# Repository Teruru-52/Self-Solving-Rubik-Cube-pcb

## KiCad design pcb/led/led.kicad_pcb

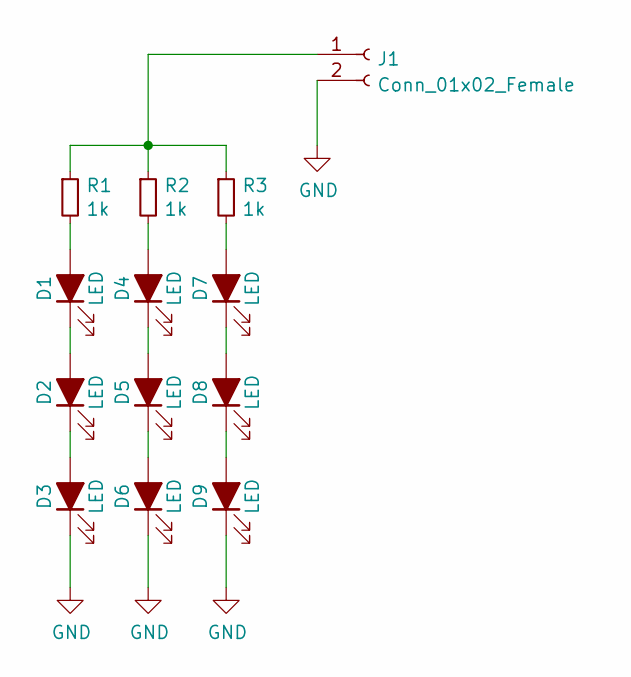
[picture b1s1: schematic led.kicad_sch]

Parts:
D1, D2, D3, D4, D5, D6, D7, D8, D9: LED; OSW5DLS1C1A
J1: Conn_01x02_Female; PinSocket_1x02_P2.54mm_Vertical
R1, R2, R3: 1k; R_0805_2012Metric_Pad1.20x1.40mm_HandSolder

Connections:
GND: D3.1 (K), D6.1 (K), D9.1 (K), J1.2
unnamed: D1.1 (K), D2.2 (A)
unnamed: D1.2 (A), R1.2
unnamed: D2.1 (K), D3.2 (A)
unnamed: D4.1 (K), D5.2 (A)
unnamed: D4.2 (A), R2.2
unnamed: D5.1 (K), D6.2 (A)
unnamed: D7.1 (K), D8.2 (A)
unnamed: D7.2 (A), R3.2
unnamed: D8.1 (K), D9.2 (A)
unnamed: J1.1, R1.1, R2.1, R3.1

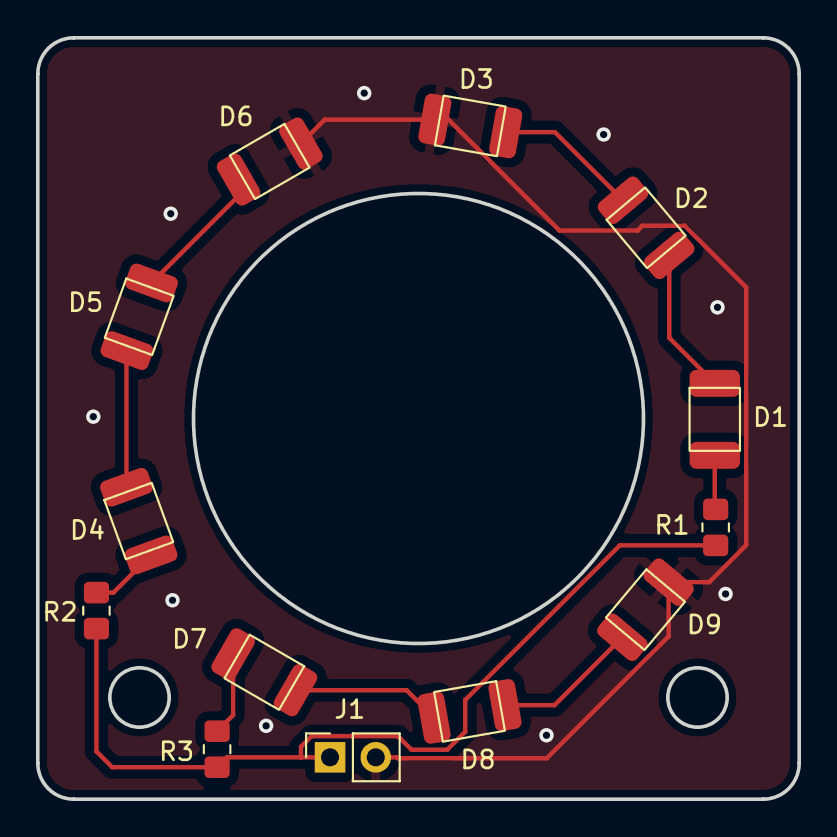
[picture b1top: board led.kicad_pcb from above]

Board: 2 copper layers, 42.3 x 42.3 mm, 13 parts (0 on the bottom side), 11 nets.

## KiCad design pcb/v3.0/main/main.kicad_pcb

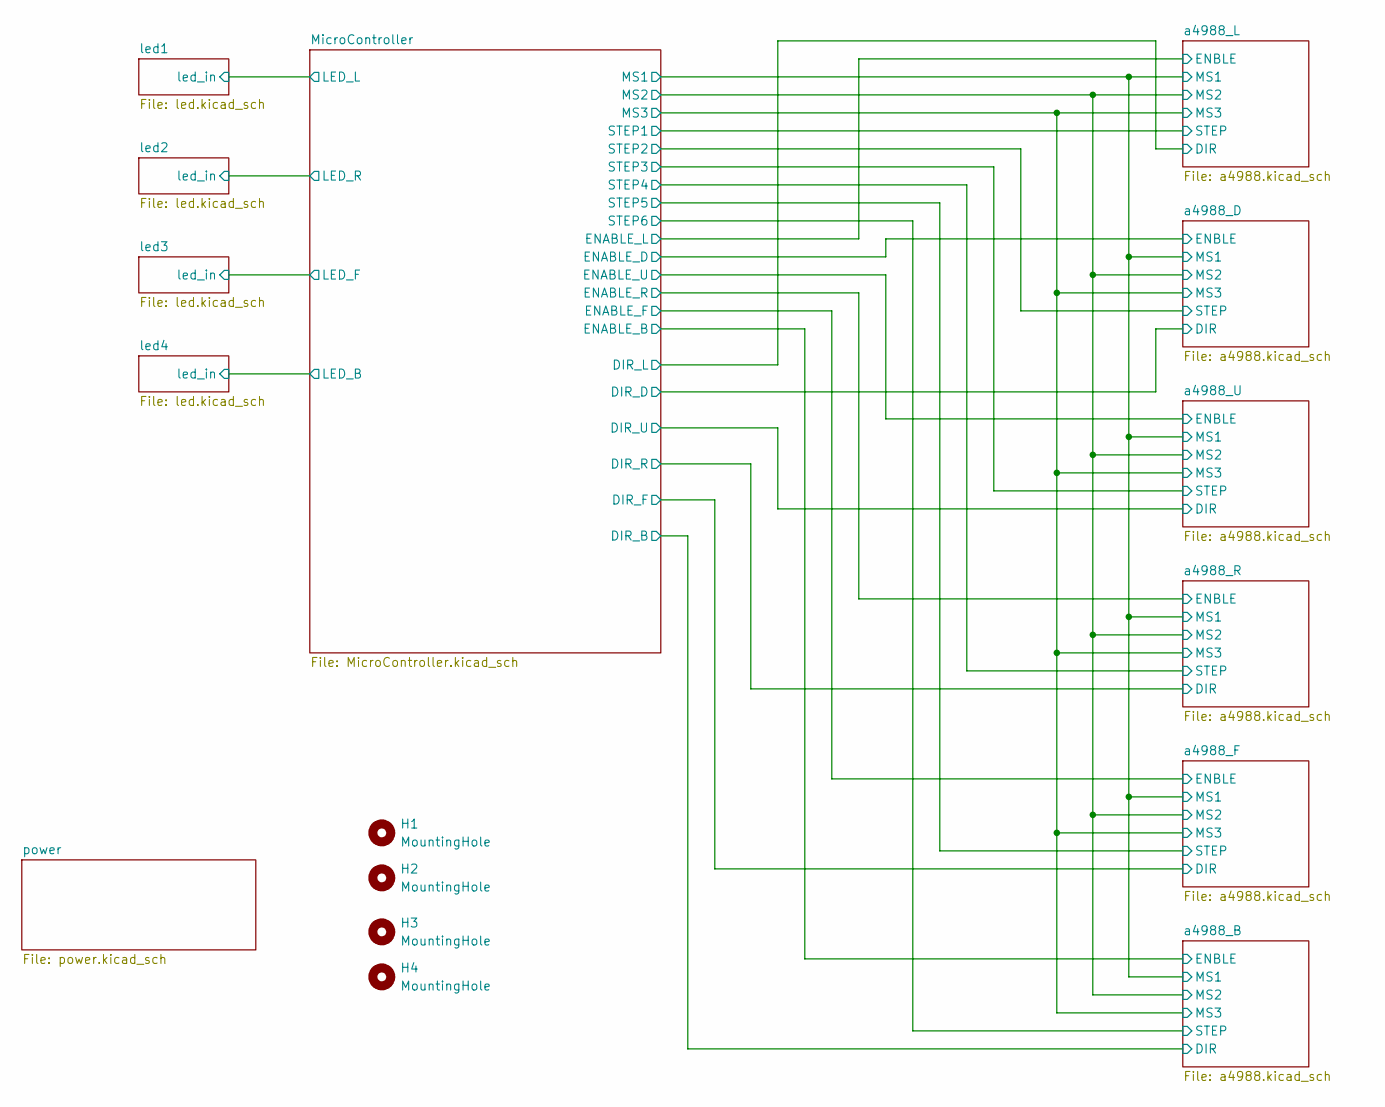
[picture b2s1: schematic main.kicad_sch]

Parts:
H1, H2, H3, H4: MountingHole; MountingHole_3.2mm_M3

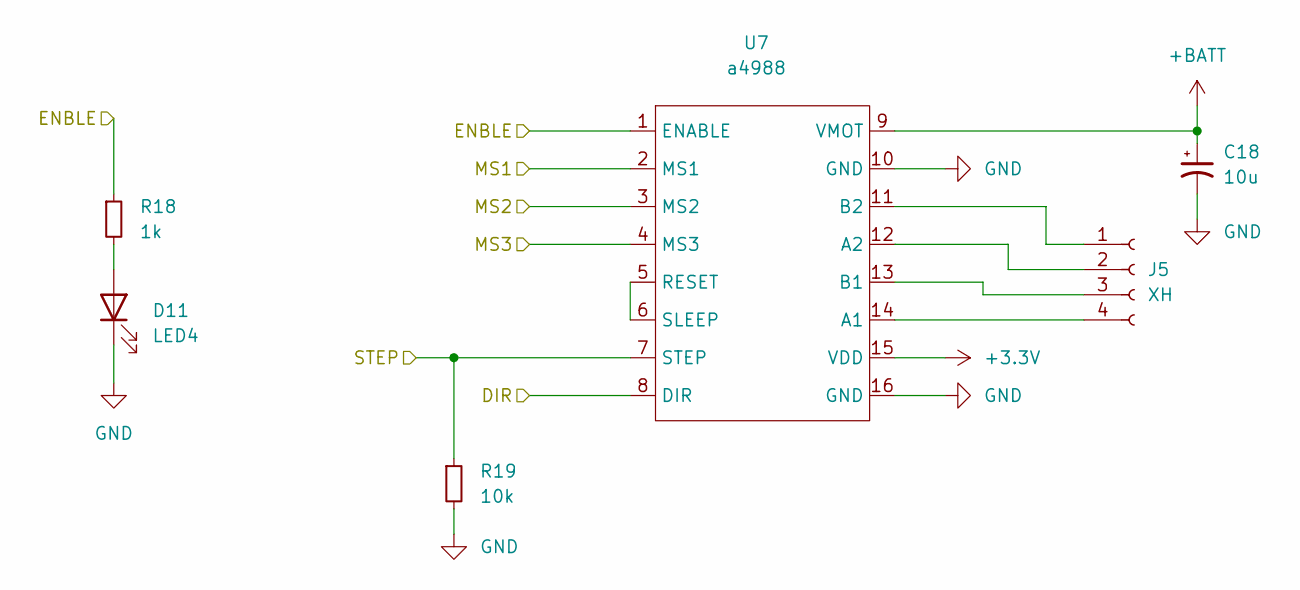
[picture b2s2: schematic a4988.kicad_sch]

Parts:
C18: 10u; CP_Radial_D5.0mm_P2.50mm
D11: LED4; LED_0603_1608Metric
J5: XH; JST_XH_B4B-XH-A_1x04_P2.50mm_Vertical
R18: 1k; R_0603_1608Metric_Pad0.98x0.95mm_HandSolder
R19: 10k; R_0603_1608Metric
U7: a4988

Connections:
+3.3V: U7.15 (VDD); also elsewhere on the board
+BATT: C18.1, U7.9 (VMOT); also elsewhere on the board
/MicroController/DIR_U: U7.8 (DIR); also elsewhere on the board
/MicroController/ENABLE_U: R18.1, U7.1 (ENABLE); also elsewhere on the board
/MicroController/MS1: U7.2 (MS1); also elsewhere on the board
/MicroController/MS2: U7.3 (MS2); also elsewhere on the board
/MicroController/MS3: U7.4 (MS3); also elsewhere on the board
/MicroController/STEP1: R19.1, U7.7 (STEP); also elsewhere on the board
GND: C18.2, D11.1 (K), R19.2, U7.10 (GND), U7.16 (GND); also elsewhere on the board
unnamed: D11.2 (A), R18.2
unnamed: J5.1, U7.11 (B2)
unnamed: J5.2, U7.12 (A2)
unnamed: J5.3, U7.13 (B1)
unnamed: J5.4, U7.14 (A1)
unnamed: U7.5 (RESET), U7.6 (SLEEP)

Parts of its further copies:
C17, C19, C20, C21, C22: 10u; CP_Radial_D5.0mm_P2.50mm
D10, D12, D13, D14, D15: LED4; LED_0603_1608Metric
J4, J6, J7, J8, J11: XH; JST_XH_B4B-XH-A_1x04_P2.50mm_Vertical
R16, R20, R22, R24, R30: 1k; R_0603_1608Metric_Pad0.98x0.95mm_HandSolder
R17, R21, R23, R25, R31: 10k; R_0603_1608Metric
U6, U8, U9, U10, U11: a4988

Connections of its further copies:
+3.3V: U6.15 (VDD), U8.15 (VDD), U9.15 (VDD), U10.15 (VDD), U11.15 (VDD); also elsewhere on the board
+BATT: C17.1, C19.1, C20.1, C21.1, C22.1, U6.9 (VMOT), U8.9 (VMOT), U9.9 (VMOT), U10.9 (VMOT), U11.9 (VMOT); also elsewhere on the board
/MicroController/DIR_B: U10.8 (DIR); also elsewhere on the board
/MicroController/DIR_D: U6.8 (DIR); also elsewhere on the board
/MicroController/DIR_F: U9.8 (DIR); also elsewhere on the board
/MicroController/DIR_L: U8.8 (DIR); also elsewhere on the board
/MicroController/DIR_R: U11.8 (DIR); also elsewhere on the board
/MicroController/ENABLE_B: R24.1, U10.1 (ENABLE); also elsewhere on the board
/MicroController/ENABLE_D: R16.1, U6.1 (ENABLE); also elsewhere on the board
/MicroController/ENABLE_F: R22.1, U9.1 (ENABLE); also elsewhere on the board
/MicroController/ENABLE_L: R20.1, U8.1 (ENABLE); also elsewhere on the board
/MicroController/ENABLE_R: R30.1, U11.1 (ENABLE); also elsewhere on the board
/MicroController/MS1: U6.2 (MS1), U8.2 (MS1), U9.2 (MS1), U10.2 (MS1), U11.2 (MS1); also elsewhere on the board
/MicroController/MS2: U6.3 (MS2), U8.3 (MS2), U9.3 (MS2), U10.3 (MS2), U11.3 (MS2); also elsewhere on the board
/MicroController/MS3: U6.4 (MS3), U8.4 (MS3), U9.4 (MS3), U10.4 (MS3), U11.4 (MS3); also elsewhere on the board
/MicroController/STEP1: R17.1, R21.1, R23.1, R25.1, R31.1, U6.7 (STEP), U8.7 (STEP), U9.7 (STEP), U10.7 (STEP), U11.7 (STEP); also elsewhere on the board
GND: C17.2, C19.2, C20.2, C21.2, C22.2, D10.1 (K), D12.1 (K), D13.1 (K), D14.1 (K), D15.1 (K), R17.2, R21.2, R23.2, R25.2, R31.2, U6.10 (GND), U6.16 (GND), U8.10 (GND), U8.16 (GND), U9.10 (GND), U9.16 (GND), U10.10 (GND), U10.16 (GND), U11.10 (GND), U11.16 (GND); also elsewhere on the board
unnamed: D10.2 (A), R16.2
unnamed: D12.2 (A), R20.2
unnamed: D13.2 (A), R22.2
unnamed: D14.2 (A), R24.2
unnamed: D15.2 (A), R30.2
unnamed: J4.1, U6.11 (B2)
unnamed: J4.2, U6.12 (A2)
unnamed: J4.3, U6.13 (B1)
unnamed: J4.4, U6.14 (A1)
unnamed: J6.1, U8.11 (B2)
unnamed: J6.2, U8.12 (A2)
unnamed: J6.3, U8.13 (B1)
unnamed: J6.4, U8.14 (A1)
unnamed: J7.1, U9.11 (B2)
unnamed: J7.2, U9.12 (A2)
unnamed: J7.3, U9.13 (B1)
unnamed: J7.4, U9.14 (A1)
unnamed: J8.1, U10.11 (B2)
unnamed: J8.2, U10.12 (A2)
unnamed: J8.3, U10.13 (B1)
unnamed: J8.4, U10.14 (A1)
unnamed: J11.1, U11.11 (B2)
unnamed: J11.2, U11.12 (A2)
unnamed: J11.3, U11.13 (B1)
unnamed: J11.4, U11.14 (A1)
unnamed: U6.5 (RESET), U6.6 (SLEEP)
unnamed: U8.5 (RESET), U8.6 (SLEEP)
unnamed: U9.5 (RESET), U9.6 (SLEEP)
unnamed: U10.5 (RESET), U10.6 (SLEEP)
unnamed: U11.5 (RESET), U11.6 (SLEEP)

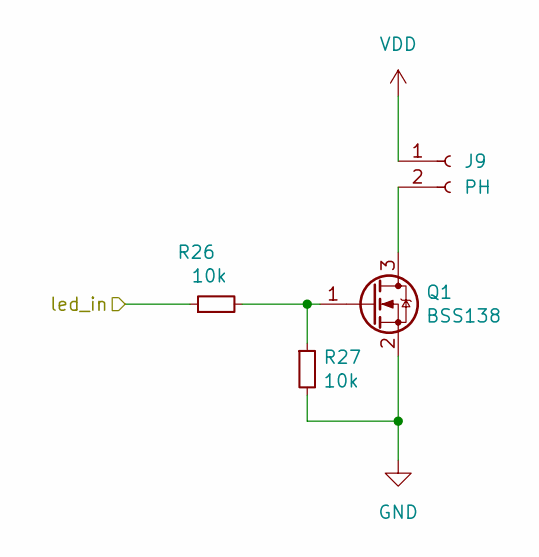
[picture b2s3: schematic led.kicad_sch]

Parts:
J9: PH; JST_PH_S2B-PH-K_1x02_P2.00mm_Horizontal
Q1: BSS138; SOT-23
R26, R27: 10k; R_0603_1608Metric_Pad0.98x0.95mm_HandSolder

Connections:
/MicroController/LED_R: R26.1; also elsewhere on the board
GND: Q1.2 (S), R27.2; also elsewhere on the board
unnamed: J9.2, Q1.3 (D)
unnamed: Q1.1 (G), R26.2, R27.1
VDD: J9.1; also elsewhere on the board

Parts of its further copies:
J10, J12, J13: PH; JST_PH_S2B-PH-K_1x02_P2.00mm_Horizontal
Q2, Q3, Q4: BSS138; SOT-23
R28, R29, R32, R33, R34, R35: 10k; R_0603_1608Metric_Pad0.98x0.95mm_HandSolder

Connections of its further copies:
/MicroController/LED_B: R34.1; also elsewhere on the board
/MicroController/LED_F: R32.1; also elsewhere on the board
/MicroController/LED_L: R28.1; also elsewhere on the board
GND: Q2.2 (S), Q3.2 (S), Q4.2 (S), R29.2, R33.2, R35.2; also elsewhere on the board
unnamed: J10.2, Q2.3 (D)
unnamed: J12.2, Q3.3 (D)
unnamed: J13.2, Q4.3 (D)
unnamed: Q2.1 (G), R28.2, R29.1
unnamed: Q3.1 (G), R32.2, R33.1
unnamed: Q4.1 (G), R34.2, R35.1
VDD: J10.1, J12.1, J13.1; also elsewhere on the board

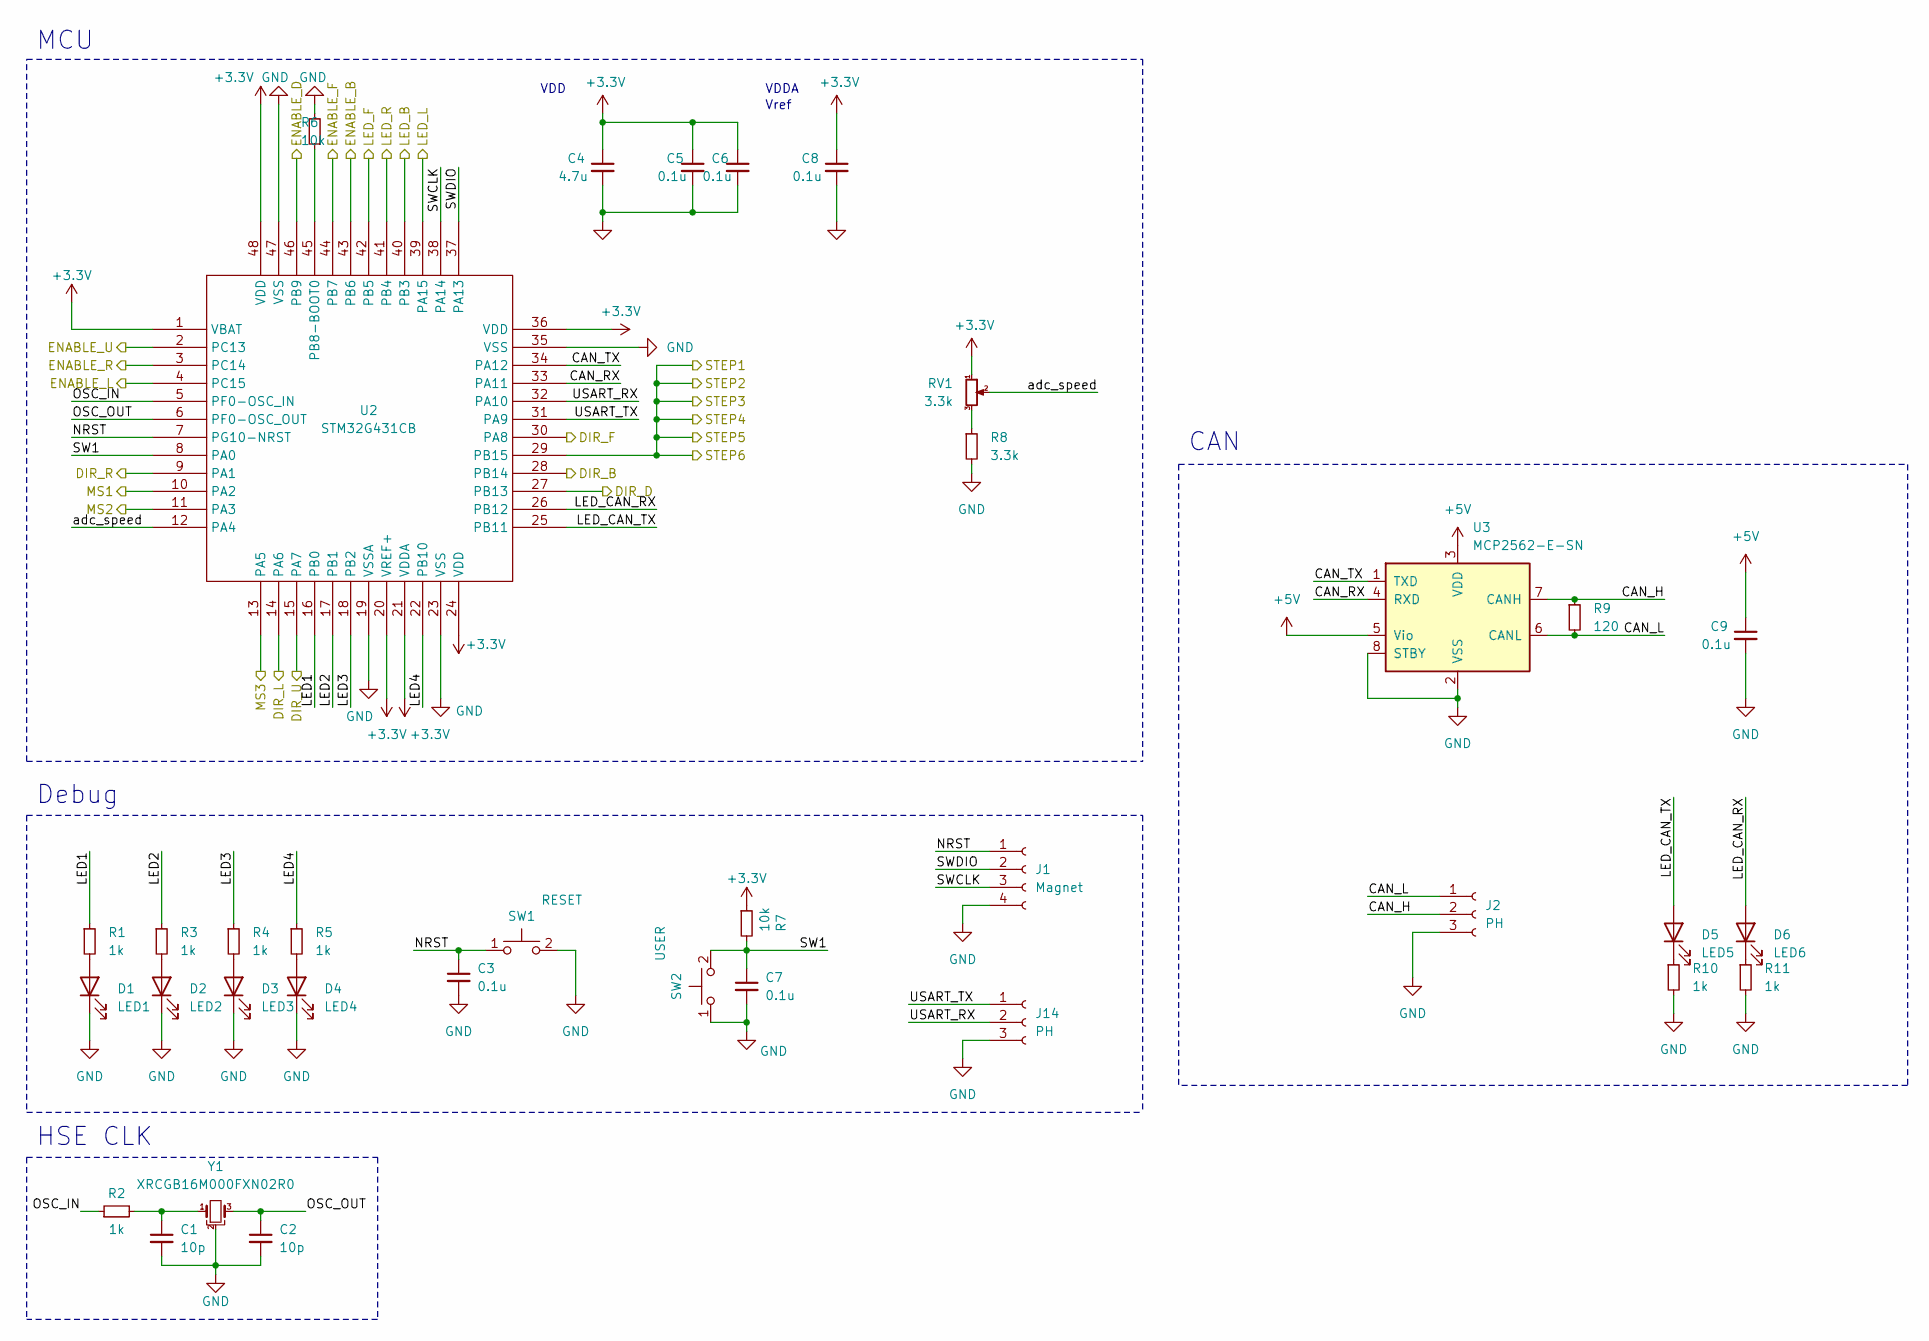
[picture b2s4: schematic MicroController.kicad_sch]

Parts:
C1, C2: 10p; C_0402_1005Metric_Pad0.74x0.62mm_HandSolder
C3, C7: 0.1u; C_0603_1608Metric_Pad1.08x0.95mm_HandSolder
C4: 4.7u; C_0603_1608Metric
C5, C6, C8, C9: 0.1u; C_0603_1608Metric
D1: LED1; LED_0603_1608Metric
D2: LED2; LED_0603_1608Metric
D3: LED3; LED_0603_1608Metric
D4: LED4; LED_0603_1608Metric
D5: LED5; LED_0603_1608Metric
D6: LED6; LED_0603_1608Metric
J1: Magnet; PinSocket_1x04_P2.54mm_Vertical
J2, J14: PH; JST_PH_S3B-PH-K_1x03_P2.00mm_Horizontal
R1, R3, R4, R5, R10, R11: 1k; R_0603_1608Metric_Pad0.98x0.95mm_HandSolder
R2: 1k; R_0402_1005Metric_Pad0.72x0.64mm_HandSolder
R6, R7: 10k; R_0603_1608Metric_Pad0.98x0.95mm_HandSolder
R8: 3.3k; R_0603_1608Metric_Pad0.98x0.95mm_HandSolder
R9: 120; R_0603_1608Metric_Pad0.98x0.95mm_HandSolder
RV1: 3.3k; Potentiometer_Vishay_T73YP_Vertical
SW1: RESET; TVAF06-A020B-R
SW2: USER; TVAF06-A020B-R
U2: STM32G431CB; LQFP-48_7x7mm_P0.5mm
U3: MCP2562-E-SN; SOIC-8_3.9x4.9mm_P1.27mm
Y1: XRCGB16M000FXN02R0; XRCGB

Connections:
+3.3V: C4.1, C5.1, C6.1, C8.1, R7.1, RV1.1, U2.1 (VBAT), U2.20 (VREF+), U2.21 (VDDA), U2.24 (VDD), U2.36 (VDD), U2.48 (VDD); also elsewhere on the board
+5V: C9.1, U3.3 (VDD), U3.5 (Vio); also elsewhere on the board
/MicroController/CAN_H: J2.2, R9.1, U3.7 (CANH)
/MicroController/CAN_L: J2.1, R9.2, U3.6 (CANL)
/MicroController/CAN_RX: U2.33 (PA11), U3.4 (RXD)
/MicroController/CAN_TX: U2.34 (PA12), U3.1 (TXD)
/MicroController/DIR_B: U2.28 (PB14); also elsewhere on the board
/MicroController/DIR_D: U2.27 (PB13); also elsewhere on the board
/MicroController/DIR_F: U2.30 (PA8); also elsewhere on the board
/MicroController/DIR_L: U2.14 (PA6); also elsewhere on the board
/MicroController/DIR_R: U2.9 (PA1); also elsewhere on the board
/MicroController/DIR_U: U2.15 (PA7); also elsewhere on the board
/MicroController/ENABLE_B: U2.43 (PB6); also elsewhere on the board
/MicroController/ENABLE_D: U2.46 (PB9); also elsewhere on the board
/MicroController/ENABLE_F: U2.44 (PB7); also elsewhere on the board
/MicroController/ENABLE_L: U2.4 (PC15); also elsewhere on the board
/MicroController/ENABLE_R: U2.3 (PC14); also elsewhere on the board
/MicroController/ENABLE_U: U2.2 (PC13); also elsewhere on the board
/MicroController/LED1: R1.1, U2.16 (PB0)
/MicroController/LED2: R3.1, U2.17 (PB1)
/MicroController/LED3: R4.1, U2.18 (PB2)
/MicroController/LED4: R5.1, U2.22 (PB10)
/MicroController/LED_B: U2.40 (PB3); also elsewhere on the board
/MicroController/LED_CAN_RX: D6.2 (A), U2.26 (PB12)
/MicroController/LED_CAN_TX: D5.2 (A), U2.25 (PB11)
/MicroController/LED_F: U2.42 (PB5); also elsewhere on the board
/MicroController/LED_L: U2.39 (PA15); also elsewhere on the board
/MicroController/LED_R: U2.41 (PB4); also elsewhere on the board
/MicroController/MS1: U2.10 (PA2); also elsewhere on the board
/MicroController/MS2: U2.11 (PA3); also elsewhere on the board
/MicroController/MS3: U2.13 (PA5); also elsewhere on the board
/MicroController/NRST: C3.1, J1.1, SW1.1, U2.7 (PG10-NRST)
/MicroController/OSC_IN: R2.1, U2.5 (PF0-OSC_IN)
/MicroController/OSC_OUT: C2.1, U2.6 (PF0-OSC_OUT), Y1.3
/MicroController/STEP1: U2.29 (PB15); also elsewhere on the board
/MicroController/SW1: C7.1, R7.2, SW2.2, U2.8 (PA0)
/MicroController/SWCLK: J1.3, U2.38 (PA14)
/MicroController/SWDIO: J1.2, U2.37 (PA13)
/MicroController/USART_RX: J14.2, U2.32 (PA10)
/MicroController/USART_TX: J14.1, U2.31 (PA9)
/MicroController/adc_speed: RV1.2, U2.12 (PA4)
GND: C1.2, C2.2, C3.2, C4.2, C5.2, C6.2, C7.2, C8.2, C9.2, D1.1 (K), D2.1 (K), D3.1 (K), D4.1 (K), J1.4, J2.3, J14.3, R6.2, R8.2, R10.2, R11.2, SW1.2, SW2.1, U2.19 (VSSA), U2.23 (VSS), U2.35 (VSS), U2.47 (VSS), U3.2 (VSS), U3.8 (STBY), Y1.2; also elsewhere on the board
unnamed: C1.1, R2.2, Y1.1
unnamed: D1.2 (A), R1.2
unnamed: D2.2 (A), R3.2
unnamed: D3.2 (A), R4.2
unnamed: D4.2 (A), R5.2
unnamed: D5.1 (K), R10.1
unnamed: D6.1 (K), R11.1
unnamed: R8.1, RV1.3
unnamed: R6.1, U2.45 (PB8-BOOT0)

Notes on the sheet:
Vref
VDD
MCU
CAN
VDDA
Debug
HSE CLK

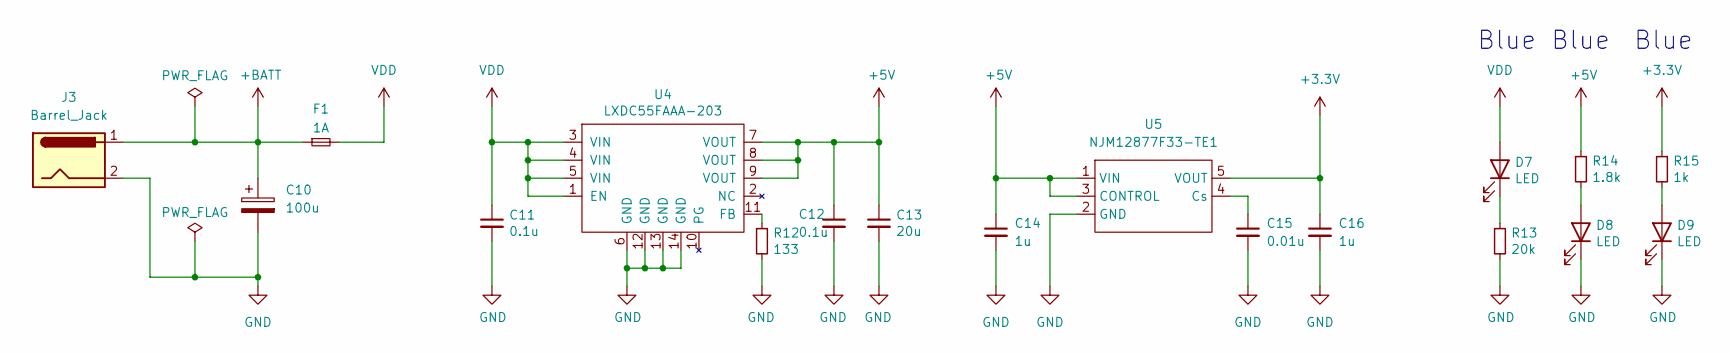
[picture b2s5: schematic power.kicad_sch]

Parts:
C10: 100u; CP_Radial_D10.0mm_P5.00mm
C11, C12: 0.1u; C_0603_1608Metric_Pad1.08x0.95mm_HandSolder
C13: 20u; C_0603_1608Metric_Pad1.08x0.95mm_HandSolder
C14, C16: 1u; C_0603_1608Metric_Pad1.08x0.95mm_HandSolder
C15: 0.01u; C_0603_1608Metric_Pad1.08x0.95mm_HandSolder
D7, D8, D9: LED; LED_0603_1608Metric
F1: 1A; Fuse_1206_3216Metric
J3: Barrel_Jack; BarrelJack_Horizontal
R12: 133; R_1206_3216Metric_Pad1.30x1.75mm_HandSolder
R13: 20k; R_0603_1608Metric_Pad0.98x0.95mm_HandSolder
R14: 1.8k; R_0603_1608Metric_Pad0.98x0.95mm_HandSolder
R15: 1k; R_0603_1608Metric_Pad0.98x0.95mm_HandSolder
U4: LXDC55FAAA-203; LXDC55FAAA203
U5: NJM12877F33-TE1; SOT-23-5_HandSoldering

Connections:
+3.3V: C16.1, R15.1, U5.5 (VOUT); also elsewhere on the board
+5V: C12.1, C13.1, C14.1, R14.1, U4.7 (VOUT), U4.8 (VOUT), U4.9 (VOUT), U5.1 (VIN), U5.3 (CONTROL); also elsewhere on the board
+BATT: C10.1, F1.1, J3.1; also elsewhere on the board
GND: C10.2, C11.2, C12.2, C13.2, C14.2, C15.2, C16.2, D8.1 (K), D9.1 (K), J3.2, R12.2, R13.2, U4.6 (GND), U4.12 (GND), U4.13 (GND), U4.14 (GND), U5.2 (GND); also elsewhere on the board
unnamed: D7.1 (K), R13.1
unnamed: D8.2 (A), R14.2
unnamed: D9.2 (A), R15.2
unnamed: R12.1, U4.11 (FB)
unnamed: C15.1, U5.4 (Cs)
VDD: C11.1, D7.2 (A), F1.2, U4.1 (EN), U4.3 (VIN), U4.4 (VIN), U4.5 (VIN); also elsewhere on the board

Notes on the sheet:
Blue

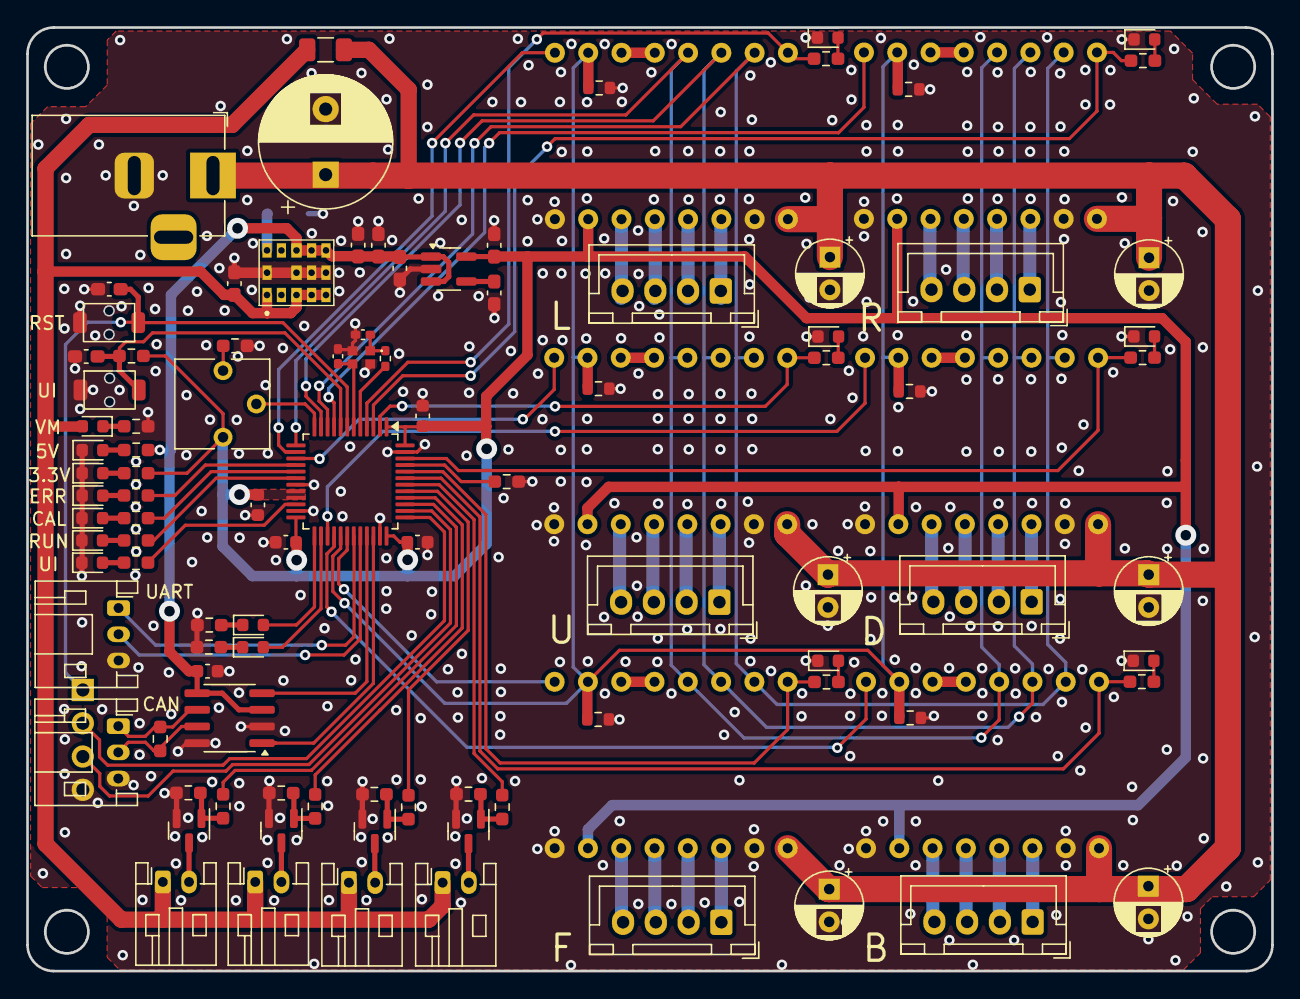
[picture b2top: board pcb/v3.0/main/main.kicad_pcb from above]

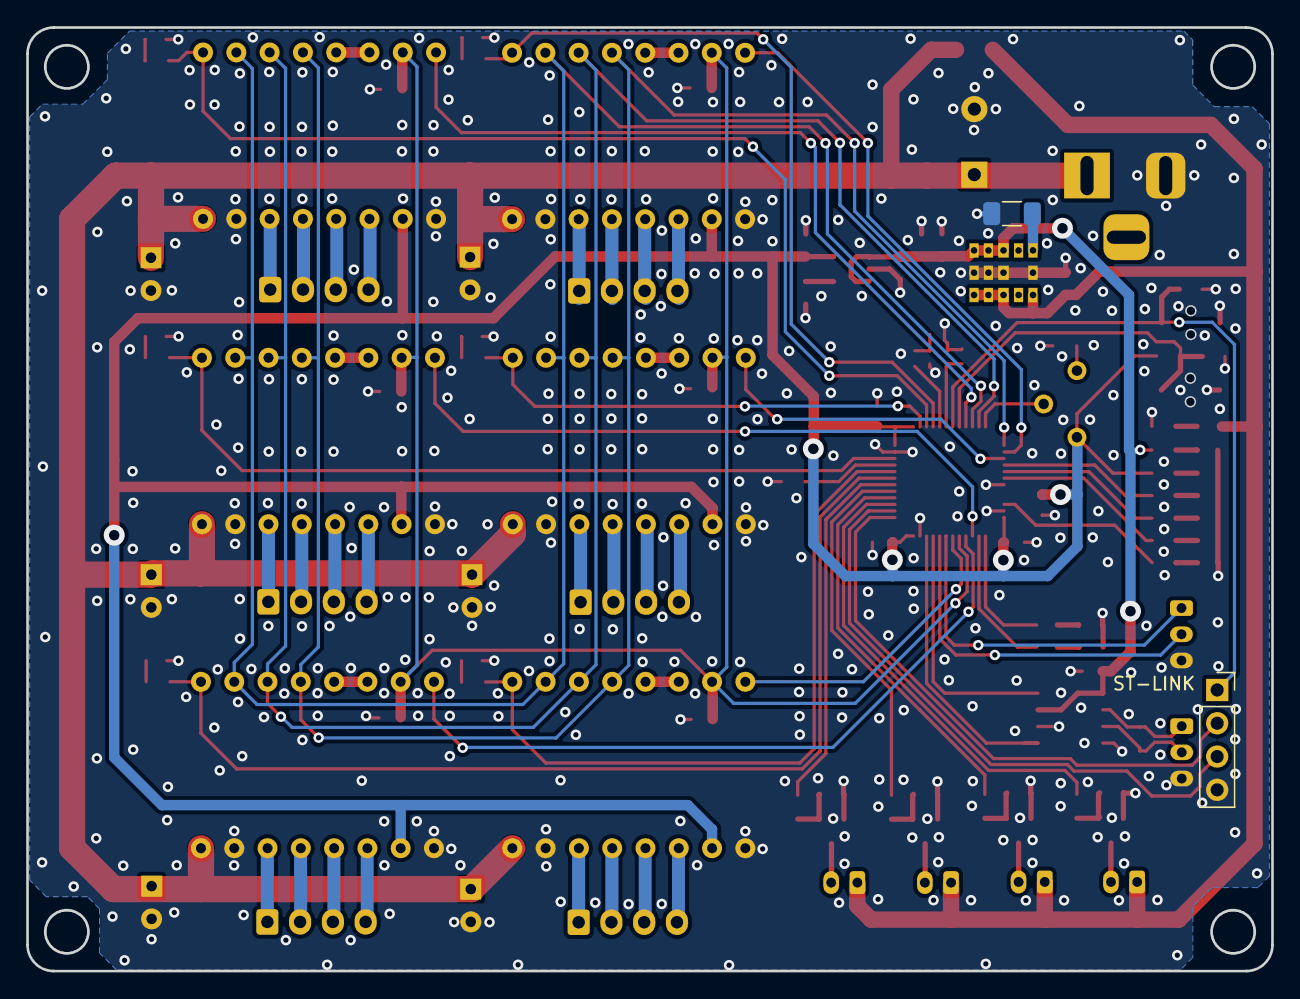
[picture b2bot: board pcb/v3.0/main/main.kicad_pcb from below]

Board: 2 copper layers, 95.0 x 72.0 mm, 109 parts (2 on the bottom side), 102 nets.

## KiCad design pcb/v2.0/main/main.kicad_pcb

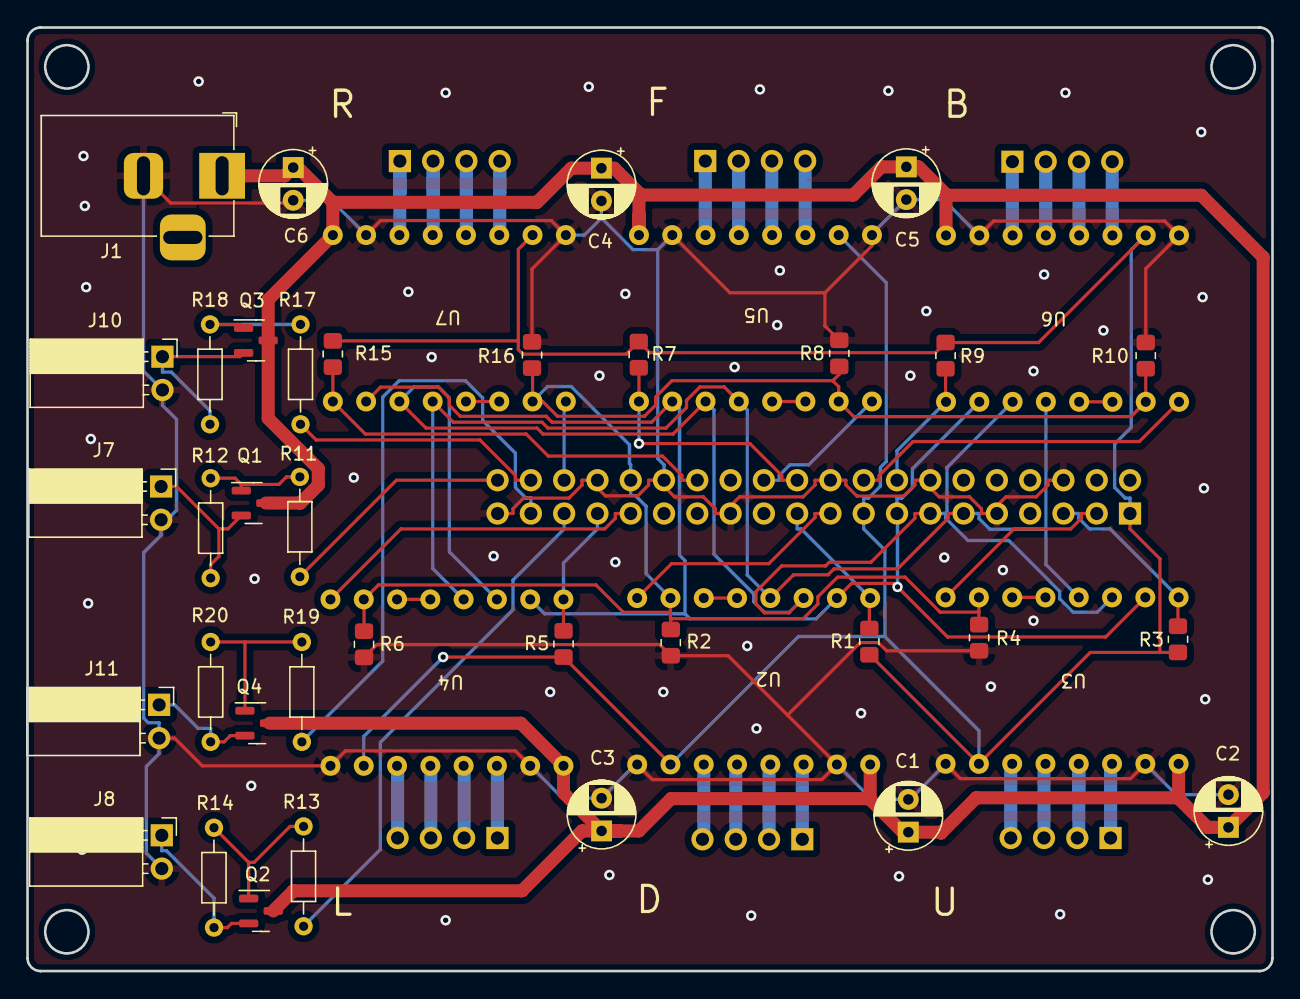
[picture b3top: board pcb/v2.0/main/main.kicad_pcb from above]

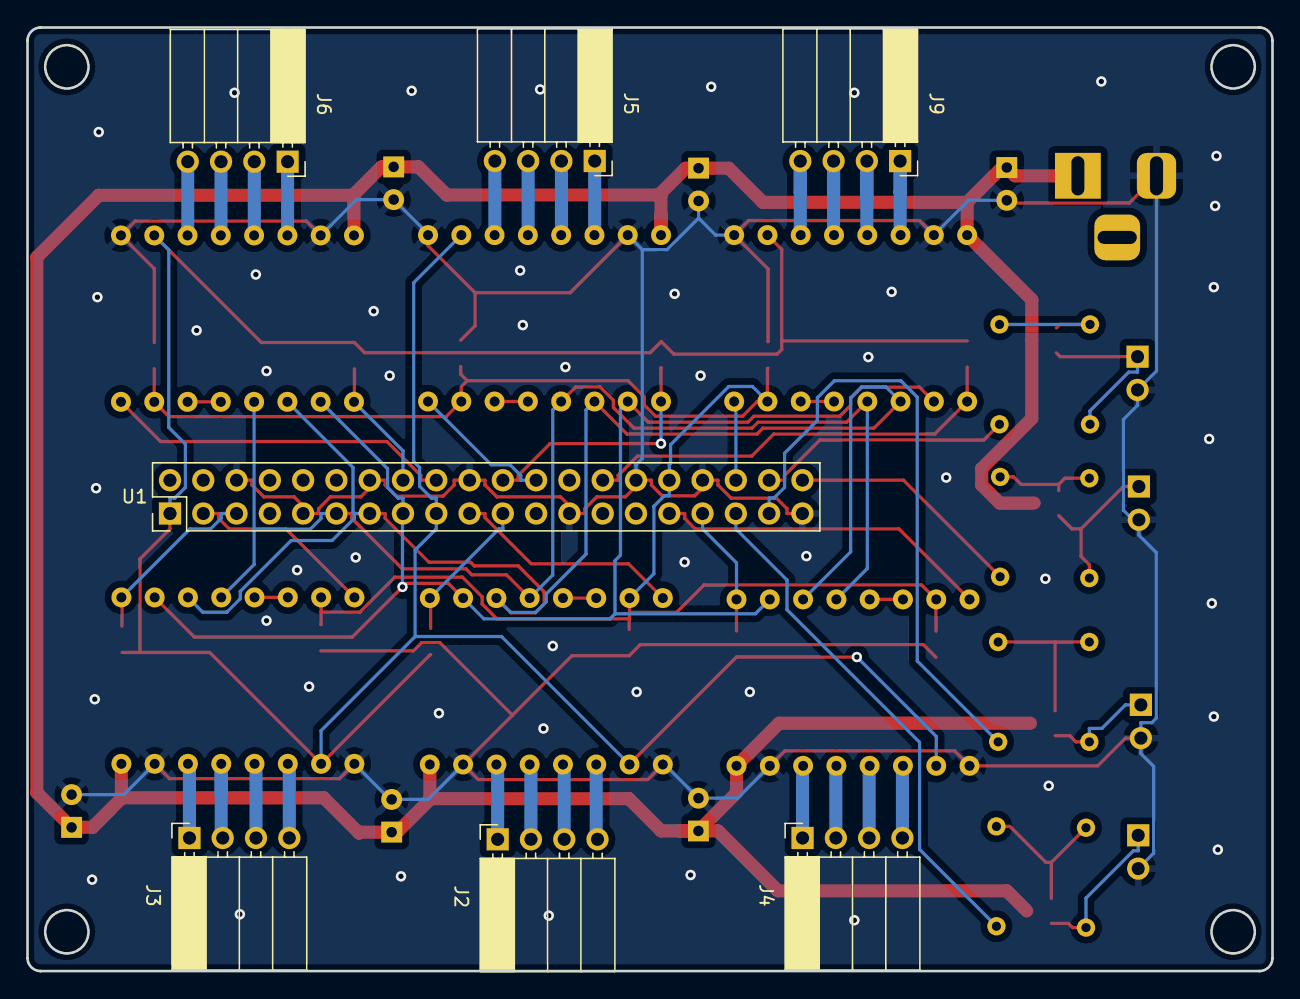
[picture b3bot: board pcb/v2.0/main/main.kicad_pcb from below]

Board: 2 copper layers, 95.0 x 72.0 mm, 48 parts (7 on the bottom side), 61 nets.

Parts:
C1, C2, C3, C4, C5, C6: 10u; CP_Radial_D5.0mm_P2.50mm
J1: Barrel_Jack; BarrelJack_Horizontal
J2, J3, J4, J5, J6, J9: Conn_01x04_Female; PinSocket_1x04_P2.54mm_Horizontal
J7, J8, J10, J11: Conn_01x02_Female; PinSocket_1x02_P2.54mm_Horizontal
Q1, Q2, Q3, Q4: BSS138; SOT-23
R1, R2, R3, R4, R5, R6, R7, R8, R9, R10, R15, R16: 10k; R_0805_2012Metric_Pad1.20x1.40mm_HandSolder
R11, R12, R13, R14, R17, R18, R19, R20: 10k; R_Axial_DIN0204_L3.6mm_D1.6mm_P7.62mm_Horizontal
U1: RaspberryPi4; PinHeader_2x20_P2.54mm_Vertical
U2, U3, U4, U5, U6, U7: a4988

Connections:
+3.3V: R1.1, R3.1, R5.1, R7.1, R9.1, R15.1, U1.1 (3V3), U1.17 (3V3), U2.15 (VDD), U3.15 (VDD), U4.15 (VDD), U5.15 (VDD), U6.15 (VDD), U7.15 (VDD)
+BATT: C1.1, C2.1, C3.1, C4.1, C5.1, C6.1, J1.1, Q1.3 (D), Q2.3 (D), Q3.3 (D), Q4.3 (D), U2.9 (VMOT), U3.9 (VMOT), U4.9 (VMOT), U5.9 (VMOT), U6.9 (VMOT), U7.9 (VMOT)
/MicroController/DIR_B: U1.18 (GPIO24), U6.8 (DIR)
/MicroController/DIR_D: U1.19 (GPIO10/MOSI), U2.8 (DIR)
/MicroController/DIR_F: U1.24 (GPIO8/CE0), U5.8 (DIR)
/MicroController/DIR_L: U1.31 (GPIO6), U4.8 (DIR)
/MicroController/DIR_R: U1.36 (GPIO16), U7.8 (DIR)
/MicroController/DIR_U: U1.3 (GPIO2/SDA), U3.8 (DIR)
/MicroController/ENABLE_B: R9.2, U1.16 (GPIO23), U6.1 (ENABLE)
/MicroController/ENABLE_D: R1.2, U1.21 (GPIO9/MISO), U2.1 (ENABLE)
/MicroController/ENABLE_F: R7.2, U1.22 (GPIO25), U5.1 (ENABLE)
/MicroController/ENABLE_L: R5.2, U1.33 (GPIO13/PWM1), U4.1 (ENABLE)
/MicroController/ENABLE_R: R15.2, U1.28 (GPIO1/ID_SC), U7.1 (ENABLE)
/MicroController/ENABLE_U: R3.2, U1.5 (GPIO3_SCL), U3.1 (ENABLE)
/MicroController/LED_B: R19.1, U1.37 (GPIO26)
/MicroController/LED_F: R17.1, U1.38 (GPIO20/PCM_DIN)
/MicroController/LED_L: R13.1, U1.35 (GPIO19/PCM_FS)
/MicroController/LED_R: R11.1, U1.40 (GPIO21/PCM_DOUT)
/MicroController/MS1: U1.15 (GPIO22), U2.2 (MS1), U3.2 (MS1), U4.2 (MS1), U5.2 (MS1), U6.2 (MS1), U7.2 (MS1)
/MicroController/MS2: U1.13 (GPIO27), U2.3 (MS2), U3.3 (MS2), U4.3 (MS2), U5.3 (MS2), U6.3 (MS2), U7.3 (MS2)
/MicroController/MS3: U1.11 (GPIO17), U2.4 (MS3), U3.4 (MS3), U4.4 (MS3), U5.4 (MS3), U6.4 (MS3), U7.4 (MS3)
/MicroController/STEP1: R2.1, R4.1, R6.1, R8.1, R10.1, R16.1, U1.32 (GPIO12/PWM0), U2.7 (STEP), U3.7 (STEP), U4.7 (STEP), U5.7 (STEP), U6.7 (STEP), U7.7 (STEP)
GND: C1.2, C2.2, C3.2, C4.2, C5.2, C6.2, J1.2, J7.2, J8.2, J10.2, J11.2, R2.2, R4.2, R6.2, R8.2, R10.2, R16.2, U1.6 (GND), U1.9 (GND), U1.14 (GND), U1.20 (GND), U1.25 (GND), U1.30 (GND), U1.34 (GND), U1.39 (GND), U2.10 (GND), U2.16 (GND), U3.10 (GND), U3.16 (GND), U4.10 (GND), U4.16 (GND), U5.10 (GND), U5.16 (GND), U6.10 (GND), U6.16 (GND), U7.10 (GND), U7.16 (GND)
unnamed: J2.1, U2.11 (B2)
unnamed: J2.2, U2.12 (A2)
unnamed: J2.3, U2.13 (B1)
unnamed: J2.4, U2.14 (A1)
unnamed: J3.1, U3.11 (B2)
unnamed: J3.2, U3.12 (A2)
unnamed: J3.3, U3.13 (B1)
unnamed: J3.4, U3.14 (A1)
unnamed: J4.1, U4.11 (B2)
unnamed: J4.2, U4.12 (A2)
unnamed: J4.3, U4.13 (B1)
unnamed: J4.4, U4.14 (A1)
unnamed: J5.1, U5.11 (B2)
unnamed: J5.2, U5.12 (A2)
unnamed: J5.3, U5.13 (B1)
unnamed: J5.4, U5.14 (A1)
unnamed: J6.1, U6.11 (B2)
unnamed: J6.2, U6.12 (A2)
unnamed: J6.3, U6.13 (B1)
unnamed: J6.4, U6.14 (A1)
unnamed: J9.1, U7.11 (B2)
unnamed: J9.2, U7.12 (A2)
unnamed: J9.3, U7.13 (B1)
unnamed: J9.4, U7.14 (A1)
unnamed: Q1.1 (G), R11.2, R12.1
unnamed: J7.1, Q1.2 (S), R12.2
unnamed: Q2.1 (G), R13.2, R14.1
unnamed: J8.1, Q2.2 (S), R14.2
unnamed: Q3.1 (G), R17.2, R18.1
unnamed: J10.1, Q3.2 (S), R18.2
unnamed: Q4.1 (G), R19.2, R20.1
unnamed: J11.1, Q4.2 (S), R20.2
unnamed: U2.5 (RESET), U2.6 (SLEEP)
unnamed: U3.5 (RESET), U3.6 (SLEEP)
unnamed: U4.5 (RESET), U4.6 (SLEEP)
unnamed: U5.5 (RESET), U5.6 (SLEEP)
unnamed: U6.5 (RESET), U6.6 (SLEEP)
unnamed: U7.5 (RESET), U7.6 (SLEEP)

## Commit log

2025-03-05 refactor: directory structure
2025-03-05 chore: edit .gitignore
2025-03-05 feat: update schematic
2025-03-05 feat: parts alignment (wip)
2025-03-08 feat: finish pcb design
2025-03-08 fix: add UART
2025-04-05 chore: add pdf
2025-10-12 feat: add led board
